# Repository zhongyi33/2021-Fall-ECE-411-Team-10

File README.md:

# 2021-Fall-ECE-411-Team-10

Group member: Bradley Huntington, Lihong Zhao, Tianshu Chu, Zhongyi Xu

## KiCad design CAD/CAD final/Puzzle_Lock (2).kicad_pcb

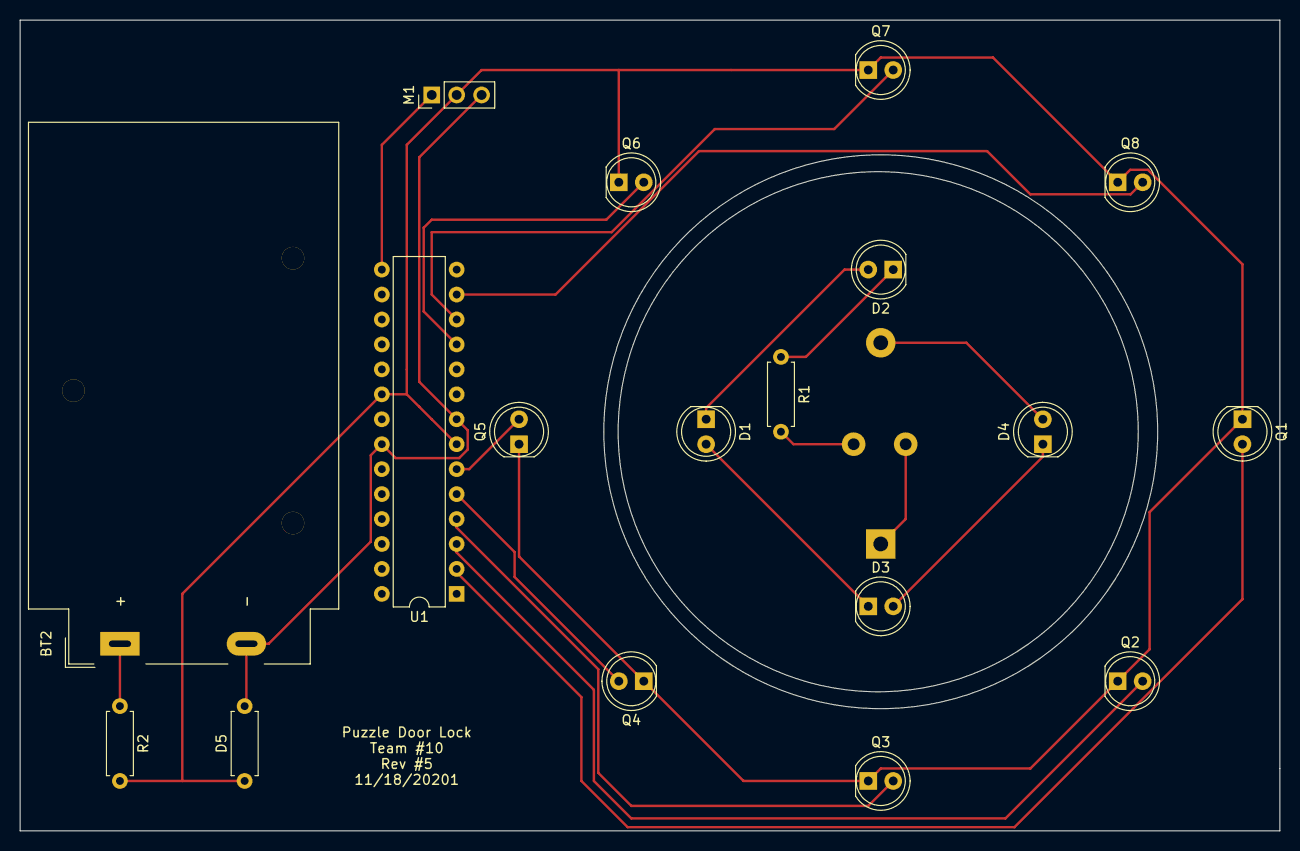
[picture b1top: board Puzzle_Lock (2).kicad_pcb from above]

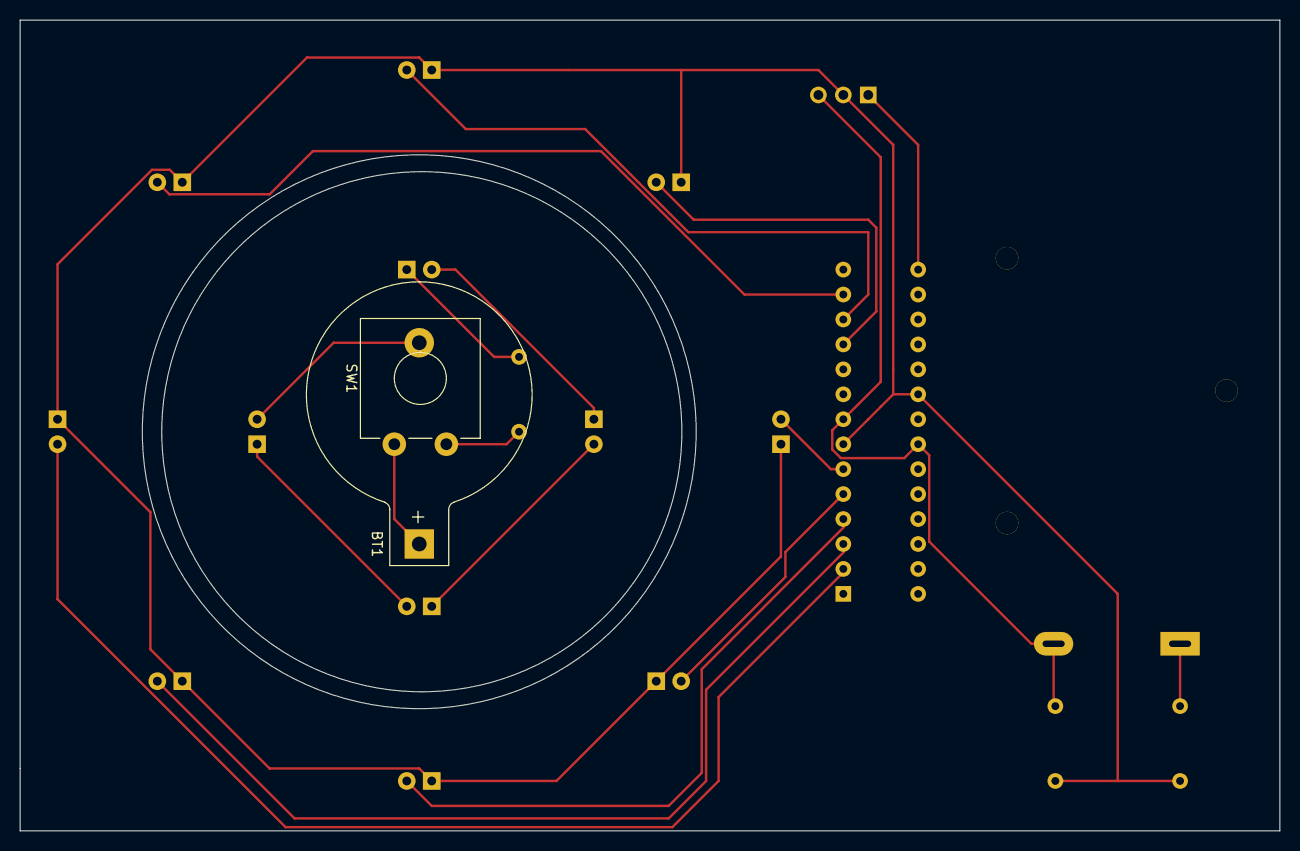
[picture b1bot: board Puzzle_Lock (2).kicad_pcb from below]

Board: 2 copper layers, 128.3 x 82.5 mm, 20 parts (2 on the bottom side), 19 nets.

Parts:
BT1: 3V; BatteryHolder_Keystone_103_1x20mm
BT2: 9; BatteryHolder_MPD_BA9VPC_1xPP3
D1, D2, D3, D4: LED; LED_D5.0mm
D5: 5.1V; R_Axial_DIN0207_L6.3mm_D2.5mm_P7.62mm_Horizontal
M1: Motor_Servo; PinHeader_1x03_P2.54mm_Vertical
Q1, Q2, Q3, Q4, Q5, Q6, Q7, Q8: Q_Photo_NPN; LED_D5.0mm
R1: 100; R_Axial_DIN0207_L6.3mm_D2.5mm_P7.62mm_Horizontal
R2: 1K; R_Axial_DIN0207_L6.3mm_D2.5mm_P7.62mm_Horizontal
SW1: _; SW_CW_GPTS203211B
U1: ATmega8L-8PU; DIP-28_W7.62mm

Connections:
unnamed: BT1.1, SW1.1
unnamed: BT1.2, D4.2
unnamed: BT2.1, R2.1
unnamed: BT2.2, D5.2, M1.3, U1.8, U1.22
unnamed: D1.1, D2.2
unnamed: D1.2, D3.1
unnamed: D2.1, R1.1
unnamed: D3.2, D4.1
unnamed: D5.1, M1.2, Q1.1, Q2.1, Q3.1, Q4.1, Q5.1, Q6.1, Q7.1, Q8.1, R2.2, U1.7, U1.20
unnamed: M1.1, U1.15
unnamed: Q1.2, U1.2
unnamed: Q2.2, U1.3
unnamed: Q3.2, U1.4
unnamed: Q4.2, U1.5
unnamed: Q5.2, U1.6
unnamed: Q6.2, U1.11
unnamed: Q7.2, U1.12
unnamed: Q8.2, U1.13
unnamed: R1.2, SW1.2

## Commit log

2021-10-19 product design spcification
2021-10-21 upload PDS
2021-10-29 add the Breadboard Prototype at 10/28/2021
2021-11-10 week7: rough draft of CAD
2021-11-10 week 7: upload level 0 and level 1 block diagram
2021-11-11 week 7: upload level 0& level 1 block diagram
2021-11-11 Week6 : Team 10 Project Schedule
2021-11-11 add level 0 picture
2021-11-15 Create CAD
2021-11-15 Create 1
2021-11-15 Update 1
2021-11-15 Create level1 block diagram
2021-11-15 week 7 : rough draft of CAD
2021-11-15 level0& level1 block diagram(assignment for wk 7)
2021-11-17 Code for lock
2021-11-17 Create code in txt.
2021-11-17 Add puzzle lock code
2021-11-17 Add puzzle code in C++
2021-12-02 Add test plan
2021-12-08 added the function to display the current signal
2021-12-09 Add BOM
2021-12-09 Add PCB finals
2021-12-09 add board and key pictures
2022-10-11 Created using Colaboratory
